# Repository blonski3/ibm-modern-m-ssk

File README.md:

# IBM Model M SSK Wireless
*Opracowanie i wykonanie układu sterującego klawiaturą mechaniczną*. Bezprzewodowa modernizacja IBM Model M SSK: nRF52840 + nPM1300, własna membrana FPC z diodą na klawisz, firmware ZMK.

## Struktura repozytorium

```
hardware/controller/   projekt KiCad 10: motherboard + daughterboard (jedna PCB, DB wyłamywany)
hardware/membrane/     projekt KiCad 10: membrana FPC, matryca 6 × 17
hardware/lib/          wspólna biblioteka: symbole, footprinty, modele 3D
docs/                  CHANGELOG.md, HARDWARE_DECISIONS.md, datasheets/, diagrams/
mechanics/             pomiary i eksporty z Onshape
reference/             projekty referencyjne (Nordic, FSSK v1.00)
tools/                 skrypty pomocnicze (np. check_3d_paths.py)
```

Decyzje projektowe i ich uzasadnienia: `docs/HARDWARE_DECISIONS.md`; historia zmian: `docs/CHANGELOG.md`.

## Resources

[Bolt Mod, A Comprehensive Tutorial: IBM Model M SSK 1991](https://imgur.com/gallery/bolt-mod-comprehensive-tutorial-ibm-model-m-ssk-1991-arUYken)

[FSSK v1.00 - Installation & Users Manual](https://deskthority.net/viewtopic.php?t=13551)

[Request for Permission to Integrate Zephyr PF1550 PMIC Drivers into ZMK #2958](https://github.com/zmkfirmware/zmk/issues/2958)

[nRF52840 Product Specification v1.5](https://docs.nordicsemi.com/viewer/book-attachment/de~7rocmcN70bRHnA4~zJA/H1GC97m6GZQEaMxKCN6OOg-de~7rocmcN70bRHnA4~zJA)

[nPM1300 Product Specification v1.3](https://docs.nordicsemi.com/viewer/book-attachment/ZO1FVHHS04YNNMSlbsZ0Kg/KbFbu1gXgIMOyTgBK7q46A-ZO1FVHHS04YNNMSlbsZ0Kg)

[Keyboard Layout Editor NG - IBM Model M](https://editor.keyboard-tools.xyz/#share=NobwRAhgrgLgFgewE5gFxgEYBsEDswA0YuEAtgKZpgCSAQgLIAEAyswNKP0IAm5WnhMAGcADhADGAS1wBzAPoBPNACYADADoAHABYAvgVCQ0q-WELgAHmgCMpwfaLmwV1BoCsdx17MFLx9R7eDj5+rgGePmYAugbgSqi2QUmRwanJDqHW4ekxhgDuNtkp6SXFZU4FCUVOLu4R9rnglVkA7IHlpWkdTSrqyu1gjWCVyn0DnRPFPVVtnqGjA0PN1b7ONkTL49Mtc8OFW2sJG-u7tSspQy7Wo21E8QC0AMy7y-12S4VvQUMPysdVi1ih2sekclxs2juaHuoOiUSAA)

[WR-PHD Pin Header drawing](https://www.we-online.com/components/products/datasheet/61300811021.pdf)

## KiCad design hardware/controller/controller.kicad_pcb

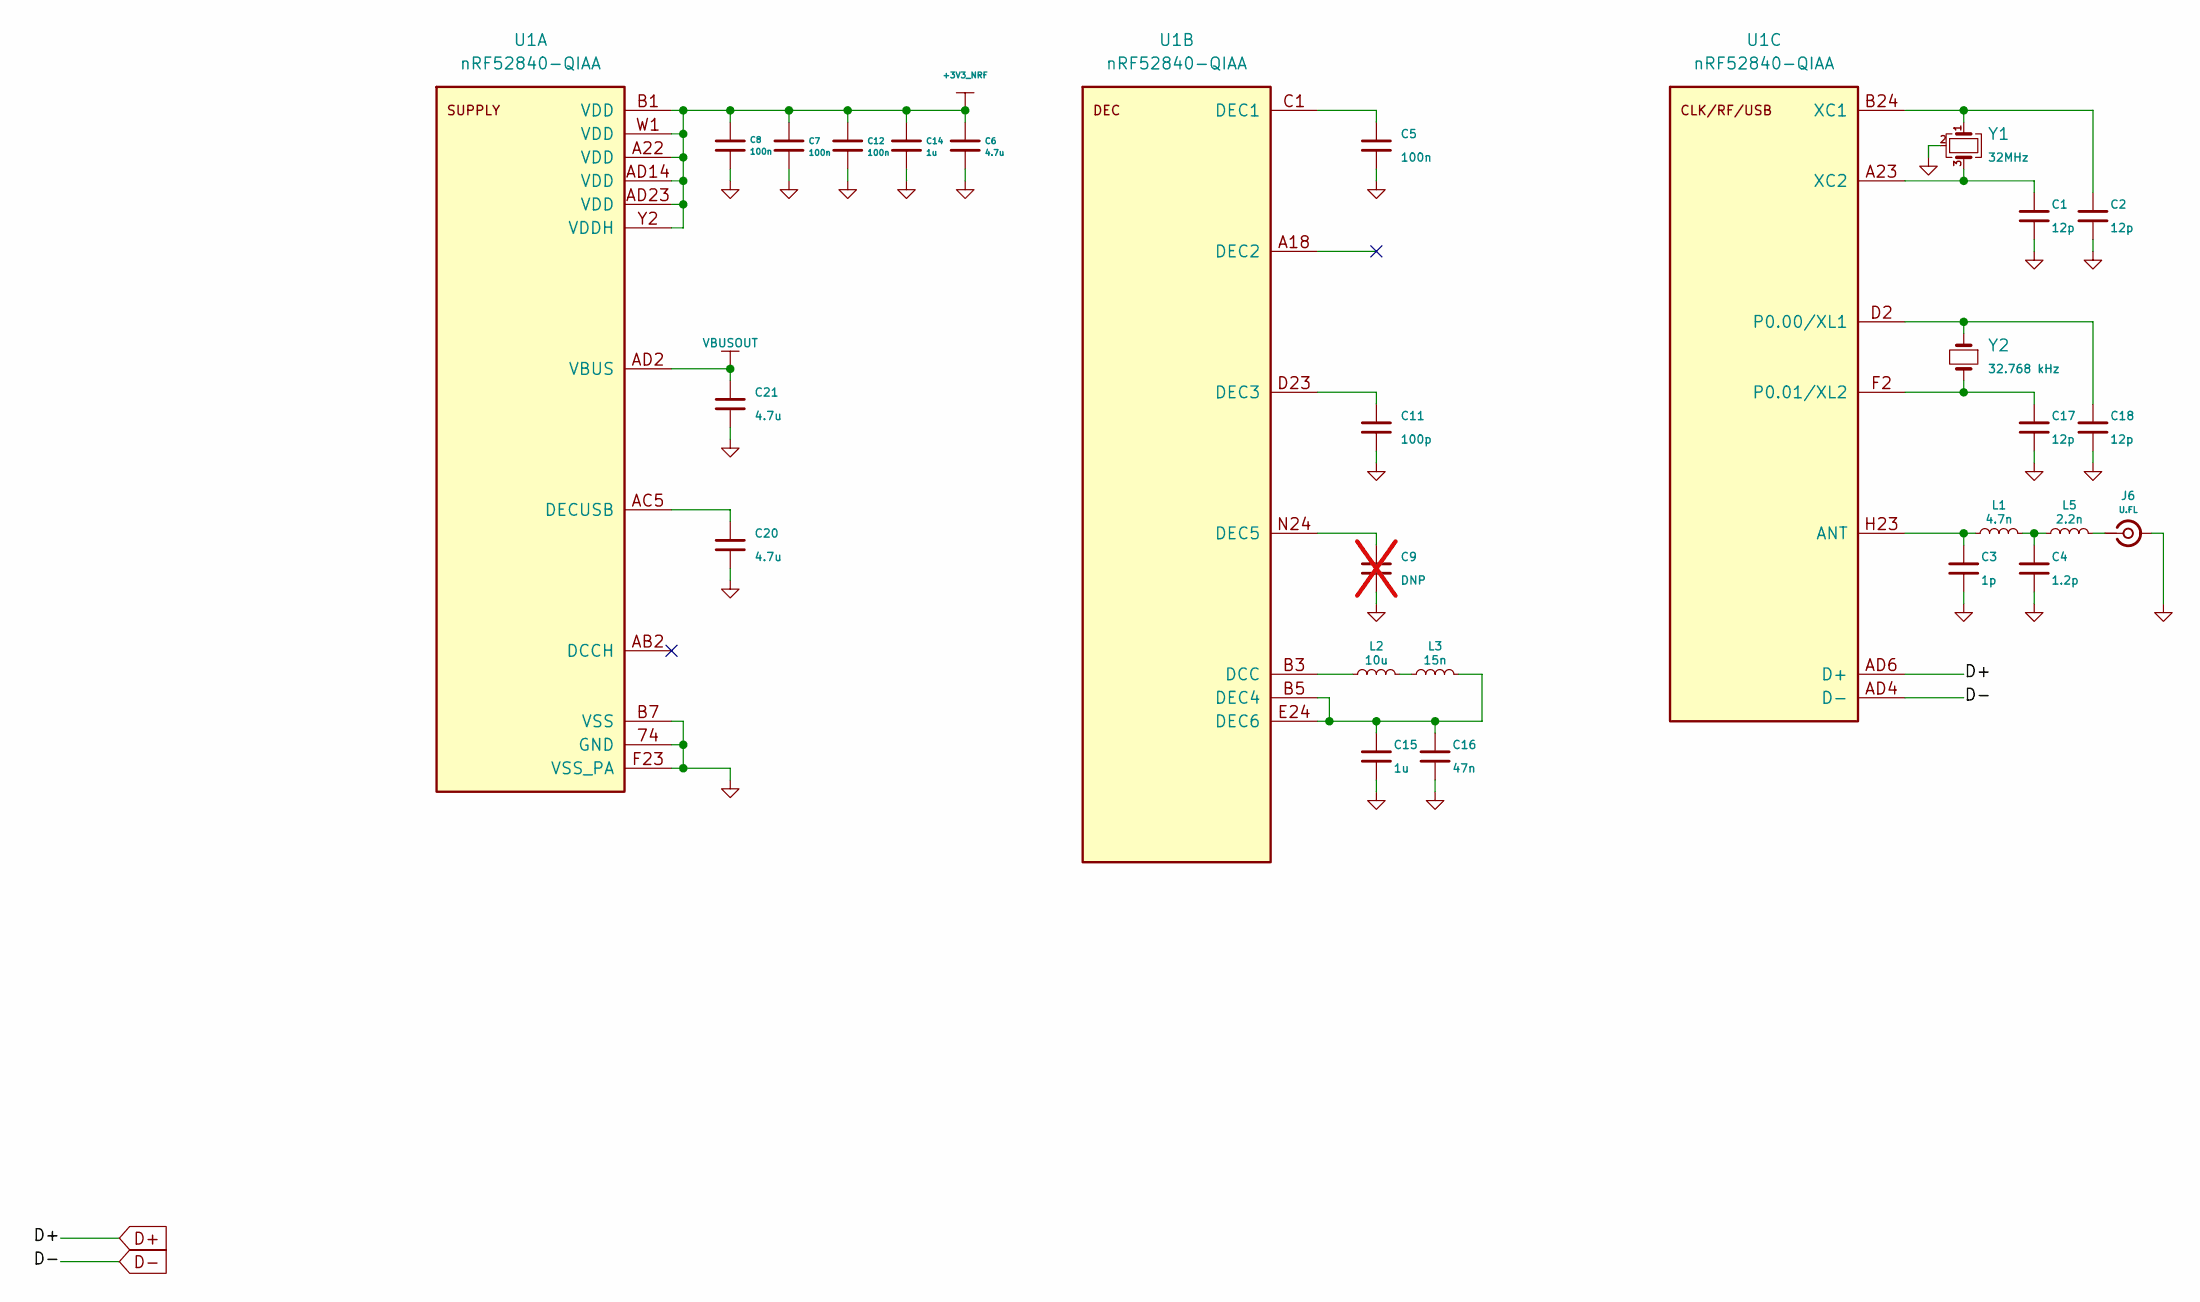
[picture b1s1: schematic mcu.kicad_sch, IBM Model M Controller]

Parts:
C1, C2, C17, C18: 12p; C_0402_1005Metric; PART NUMBER 0402CG120J500NT; LCSC Part C1547
C3: 1p; C_0402_1005Metric; PART NUMBER 0402CG1R0C500NT; LCSC Part C1550
C4: 1.2p; C_0402_1005Metric; PART NUMBER 0402CG1R2C500NT; LCSC Part C1551
C5, C7, C8, C12: 100n; C_0402_1005Metric; PART NUMBER CL05B104KO5NNNC; LCSC Part C1525
C6, C20, C21: 4.7u; C_0603_1608Metric; PART NUMBER CL10A475KO8NNNC; LCSC Part C19666
C9: DNP; C_0402_1005Metric; not fitted
C11: 100p; C_0402_1005Metric; PART NUMBER 0402CG101J500NT; LCSC Part C1546
C14, C15: 1u; C_0603_1608Metric; PART NUMBER CL10A105KB8NNNC; LCSC Part C15849
C16: 47n; C_0603_1608Metric; PART NUMBER CL10B473KB8NNNC; LCSC Part C1622
J6: U.FL; IPEX-SMD_4P-L2.6-W2.6-LS3.0_GT-RF1125A-01G; PART NUMBER U.FL-IPEX-1; LCSC Part C53433123
L1: 4.7n; L_0402_1005Metric; LCSC Part C304335
L2: 10u; L_0603_1608Metric; LCSC Part C86083
L3: 15n; L_0402_1005Metric; LCSC Part C381880
L5: 2.2n; L_0402_1005Metric; PART NUMBER CLH1005T-2N2S-S-NP; LCSC Part C142238
U1: nRF52840-QIAA; AQFN50P700X700X85_HS-74N; PART NUMBER NRF52840-QIAA-R; LCSC Part C190794
Y1: 32MHz; Crystal_SMD_2016-4Pin_2.0x1.6mm; PART NUMBER NX2016SA-32MHZ-EXS00A-CS06654; LCSC Part C5441424
Y2: 32.768 kHz; Crystal_SMD_3215-2Pin; LCSC Part C99010

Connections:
+3V3_NRF: C6.1, C7.1, C8.1, C12.1, C14.2, U1.A22 (VDD), U1.AD14 (VDD), U1.AD23 (VDD), U1.B1 (VDD), U1.W1 (VDD), U1.Y2 (VDDH); also elsewhere on the board
D+: U1.AD6 (D+); also elsewhere on the board
D-: U1.AD4 (D-); also elsewhere on the board
GND: C1.2, C2.1, C3.2, C4.2, C5.1, C6.2, C7.2, C8.2, C9.2, C11.1, C12.2, C14.1, C15.2, C16.2, C17.2, C18.1, C20.2, C21.2, J6.2 (Ext), U1.74 (GND), U1.B7 (VSS), U1.F23 (VSS_PA), Y1.2 (G), Y1.4 (G); also elsewhere on the board
unnamed: C4.1, L1.2, L5.1
unnamed: J6.1 (In), L5.2
unnamed: L2.1, L3.2
unnamed: C20.1, U1.AC5 (DECUSB)
unnamed: L2.2, U1.B3 (DCC)
unnamed: C5.2, U1.C1 (DEC1)
unnamed: C11.2, U1.D23 (DEC3)
unnamed: C15.1, C16.1, L3.1, U1.B5 (DEC4), U1.E24 (DEC6)
unnamed: C9.1, U1.N24 (DEC5)
unnamed: C3.1, L1.1, U1.H23 (ANT)
unnamed: C18.2, U1.D2 (P0.00/XL1), Y2.1
unnamed: C17.1, U1.F2 (P0.01/XL2), Y2.2
unnamed: C2.2, U1.B24 (XC1), Y1.1
unnamed: C1.1, U1.A23 (XC2), Y1.3
VBUSOUT: C21.1, U1.AD2 (VBUS); also elsewhere on the board

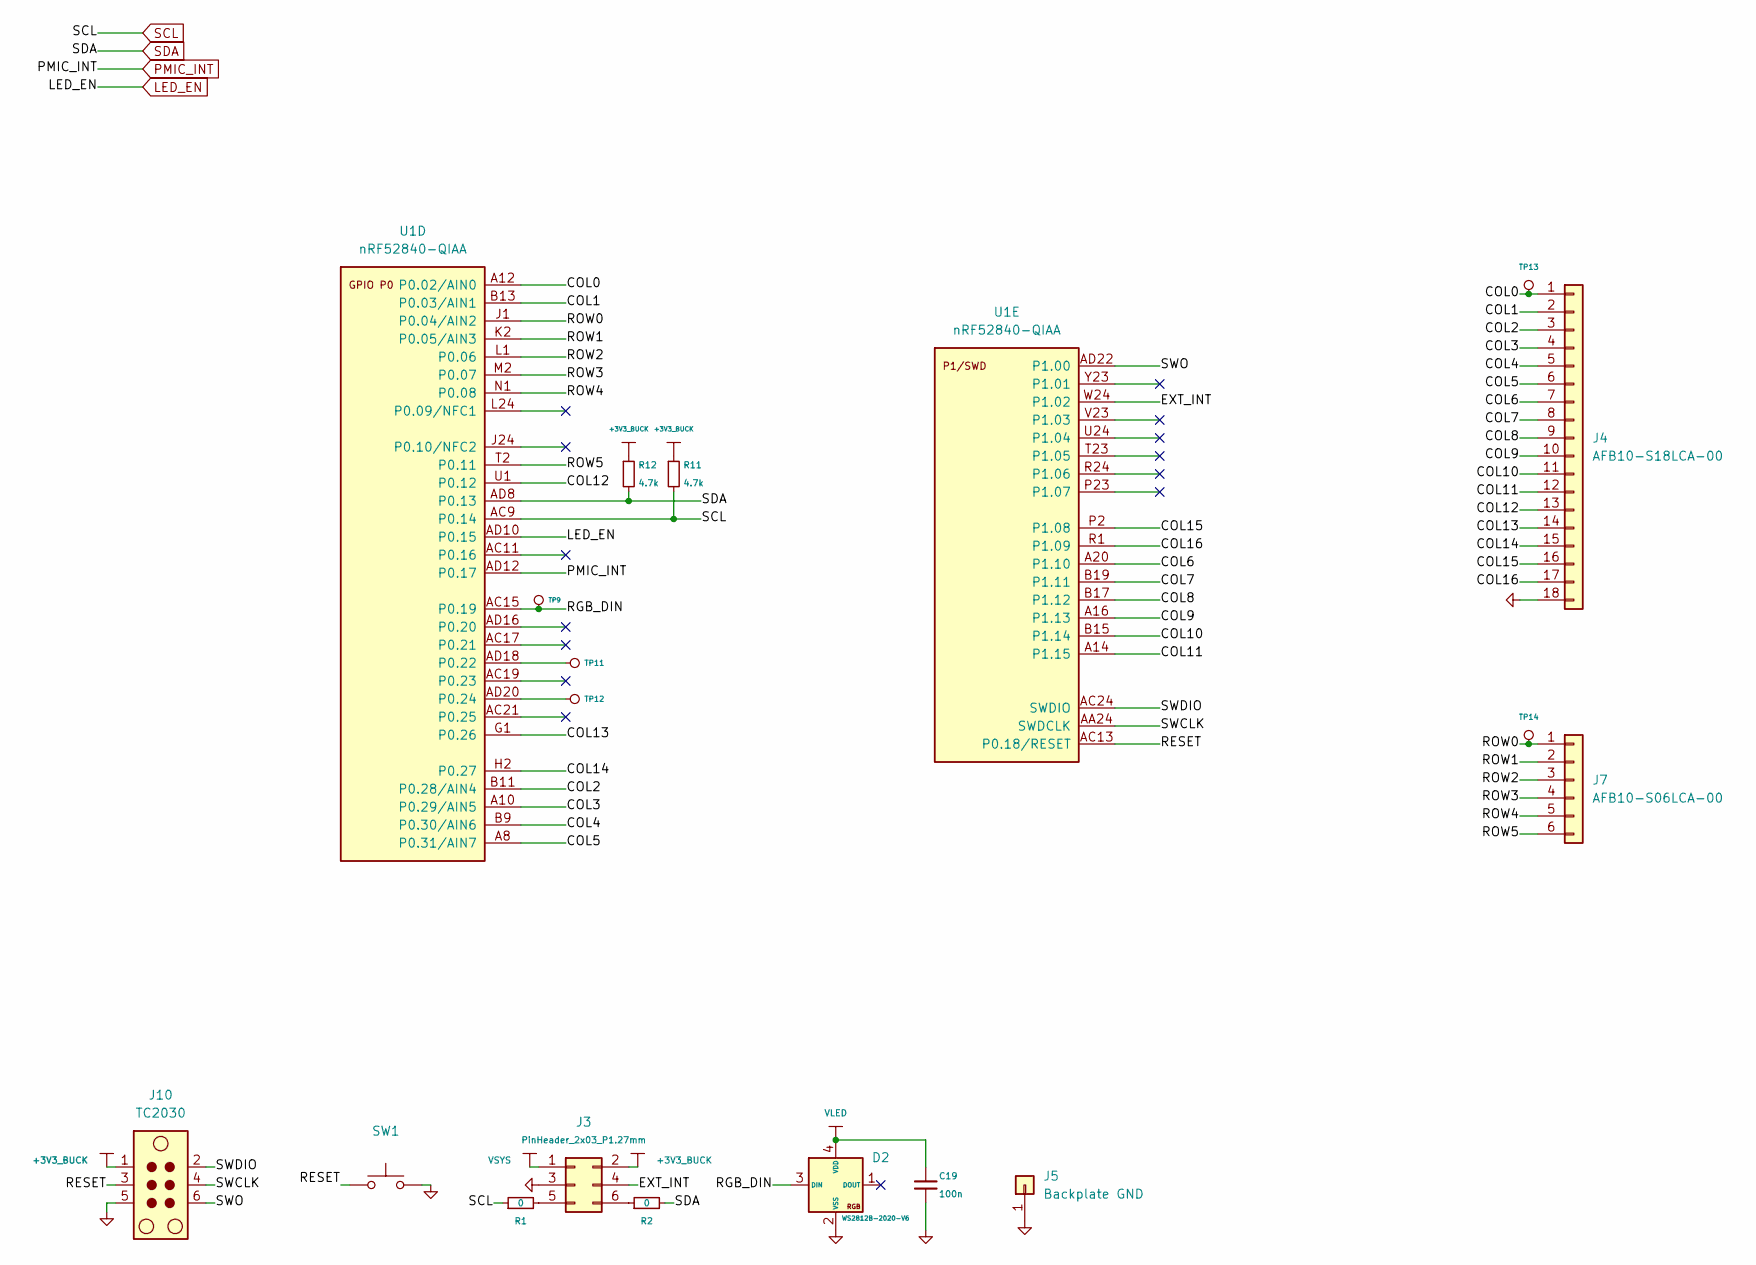
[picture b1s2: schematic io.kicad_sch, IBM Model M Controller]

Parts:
C19: 100n; C_0402_1005Metric; PART NUMBER CL05B104KO5NNNC; LCSC Part C1525
D2: WS2812B-2020-V6; LED-SMD_4P-L2.2-W2.0-P1.00_WS2815C-2020-4P; PART NUMBER WS2812B-2020-V6; LCSC Part C52917434
J3: PinHeader_2x03_P1.27mm; PinHeader_2x03_P1.27mm_Vertical_SMD
J4: AFB10-S18LCA-00; FPC-SMD_18P-P1.00_AFB10-S18LCA-00; PART NUMBER AFB10-S18LCA-00; LCSC Part C7499267
J5: Backplate GND; CONN-TH_726386-2; LCSC Part C305817
J7: AFB10-S06LCA-00; FPC-SMD_6P-P1.00_AFB10-S6LCA-00; PART NUMBER AFB10-S06LCA-00; LCSC Part C7499263
J10: TC2030; Tag-Connect_TC2030-IDC-NL_2x03_P1.27mm_Vertical
R1, R2: 0; R_0603_1608Metric; PART NUMBER 0603WAF0000T5E; LCSC Part C21189
R11, R12: 4.7k; R_0402_1005Metric; PART NUMBER 0402WGF4701TCE; LCSC Part C25900
SW1: SW_Push; SW-SMD_4P-L5.1-W5.1-P3.70-LS6.5-TL_H1.5; PART NUMBER TS-1187A-B-A-B; LCSC Part C318884
TP9, TP11, TP12, TP13, TP14: TestPoint; TestPoint_Pad
U1: nRF52840-QIAA; AQFN50P700X700X85_HS-74N; PART NUMBER NRF52840-QIAA-R; LCSC Part C190794

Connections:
+3V3_BUCK: J3.2, J10.1, R11.1, R12.1; also elsewhere on the board
/MCU IO/COL0: J4.1, TP13.1 (1_1), U1.A12 (P0.02/AIN0)
/MCU IO/COL1: J4.2, U1.B13 (P0.03/AIN1)
/MCU IO/COL2: J4.3, U1.B11 (P0.28/AIN4)
/MCU IO/COL3: J4.4, U1.A10 (P0.29/AIN5)
/MCU IO/COL4: J4.5, U1.B9 (P0.30/AIN6)
/MCU IO/COL5: J4.6, U1.A8 (P0.31/AIN7)
/MCU IO/COL6: J4.7, U1.A20 (P1.10)
/MCU IO/COL7: J4.8, U1.B19 (P1.11)
/MCU IO/COL8: J4.9, U1.B17 (P1.12)
/MCU IO/COL9: J4.10, U1.A16 (P1.13)
/MCU IO/COL10: J4.11, U1.B15 (P1.14)
/MCU IO/COL11: J4.12, U1.A14 (P1.15)
/MCU IO/COL12: J4.13, U1.U1 (P0.12)
/MCU IO/COL13: J4.14, U1.G1 (P0.26)
/MCU IO/COL14: J4.15, U1.H2 (P0.27)
/MCU IO/COL15: J4.16, U1.P2 (P1.08)
/MCU IO/COL16: J4.17, U1.R1 (P1.09)
/MCU IO/EXT_INT: J3.4, U1.W24 (P1.02)
/MCU IO/RESET: J10.3, SW1.1, U1.AC13 (P0.18/RESET)
/MCU IO/RGB_DIN: D2.3 (DIN), TP9.1 (1_1), U1.AC15 (P0.19)
/MCU IO/ROW0: J7.1, TP14.1 (1_1), U1.J1 (P0.04/AIN2)
/MCU IO/ROW1: J7.2, U1.K2 (P0.05/AIN3)
/MCU IO/ROW2: J7.3, U1.L1 (P0.06)
/MCU IO/ROW3: J7.4, U1.M2 (P0.07)
/MCU IO/ROW4: J7.5, U1.N1 (P0.08)
/MCU IO/ROW5: J7.6, U1.T2 (P0.11)
/MCU IO/SWCLK: J10.4, U1.AA24 (SWDCLK)
/MCU IO/SWDIO: J10.2, U1.AC24 (SWDIO)
/MCU IO/SWO: J10.6, U1.AD22 (P1.00)
GND: C19.2, D2.2 (VSS), J3.3, J4.18, J5.1 (Pin_1_1), J10.5, SW1.2; also elsewhere on the board
LED_EN: U1.AD10 (P0.15); also elsewhere on the board
unnamed: J3.5, R1.2
unnamed: J3.6, R2.1
unnamed: TP11.1 (1_1), U1.AD18 (P0.22)
unnamed: TP12.1 (1_1), U1.AD20 (P0.24)
PMIC_INT: U1.AD12 (P0.17); also elsewhere on the board
SCL: R1.1, R11.2, U1.AC9 (P0.14); also elsewhere on the board
SDA: R2.2, R12.2, U1.AD8 (P0.13); also elsewhere on the board
VLED: C19.1, D2.4 (VDD); also elsewhere on the board
VSYS: J3.1; also elsewhere on the board

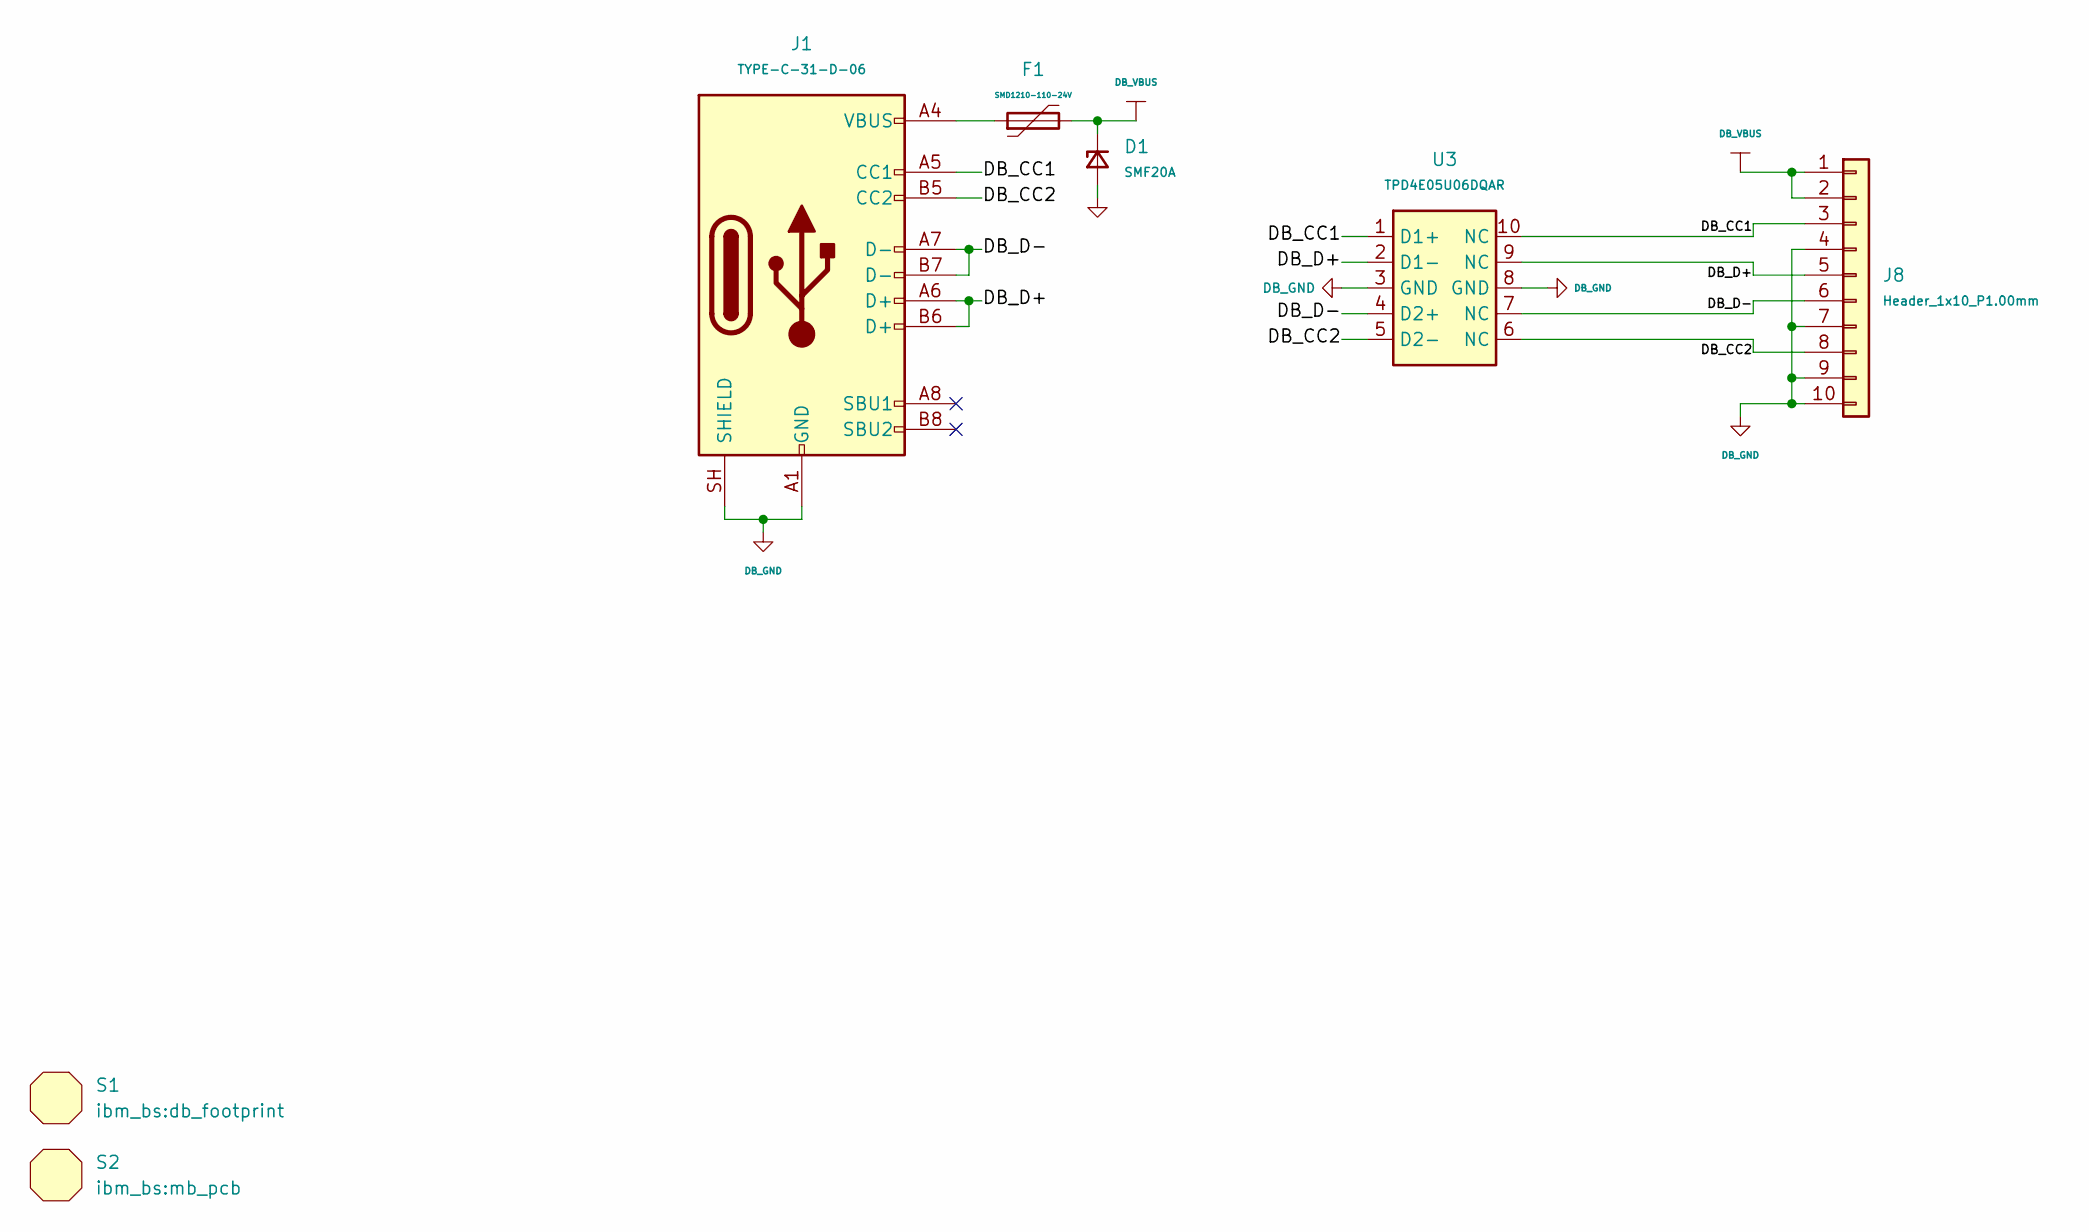
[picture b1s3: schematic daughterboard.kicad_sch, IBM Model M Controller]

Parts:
D1: SMF20A; D_SOD-123F; PART NUMBER SMF20A; LCSC Part C123788
F1: SMD1210-110-24V; Fuse_1210_3225Metric; PART NUMBER SMD1210-110-24V; LCSC Part C22436715
J1: TYPE-C-31-D-06; USB-C-SMD_TYPE-C-31-D-06; PART NUMBER TYPE-C-31-D-06; LCSC Part C2689964
J8: Header_1x10_P1.00mm; PinHeader_1x10_P1.00mm_Vertical_SMD_Pin1Left
S1: Mechanical_Shape; db_footprint
S2: Mechanical_Shape; mb_pcb
U3: TPD4E05U06DQAR; USON-10_2.5x1.0mm_P0.5mm; PART NUMBER TPD4E05U06DQAR; LCSC Part C138714

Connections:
/Daughterboard/DB_CC1: J1.A5 (CC1), J8.3, U3.1 (D1+), U3.10 (NC)
/Daughterboard/DB_CC2: J1.B5 (CC2), J8.8, U3.5 (D2-), U3.6 (NC)
/Daughterboard/DB_D+: J1.A6 (D+), J1.B6 (D+), J8.5, U3.2 (D1-), U3.9 (NC)
/Daughterboard/DB_D-: J1.A7 (D-), J1.B7 (D-), J8.6, U3.4 (D2+), U3.7 (NC)
DB_GND: D1.2 (A), J1.A1 (GND), J1.A12 (GND), J1.B1 (GND), J1.B12 (GND), J1.SH (SHIELD), J8.4, J8.7, J8.9, J8.10, U3.3 (GND), U3.8 (GND)
DB_VBUS: D1.1 (K), F1.2, J8.1, J8.2
unnamed: F1.1, J1.A4 (VBUS), J1.A9 (VBUS), J1.B4 (VBUS), J1.B9 (VBUS)

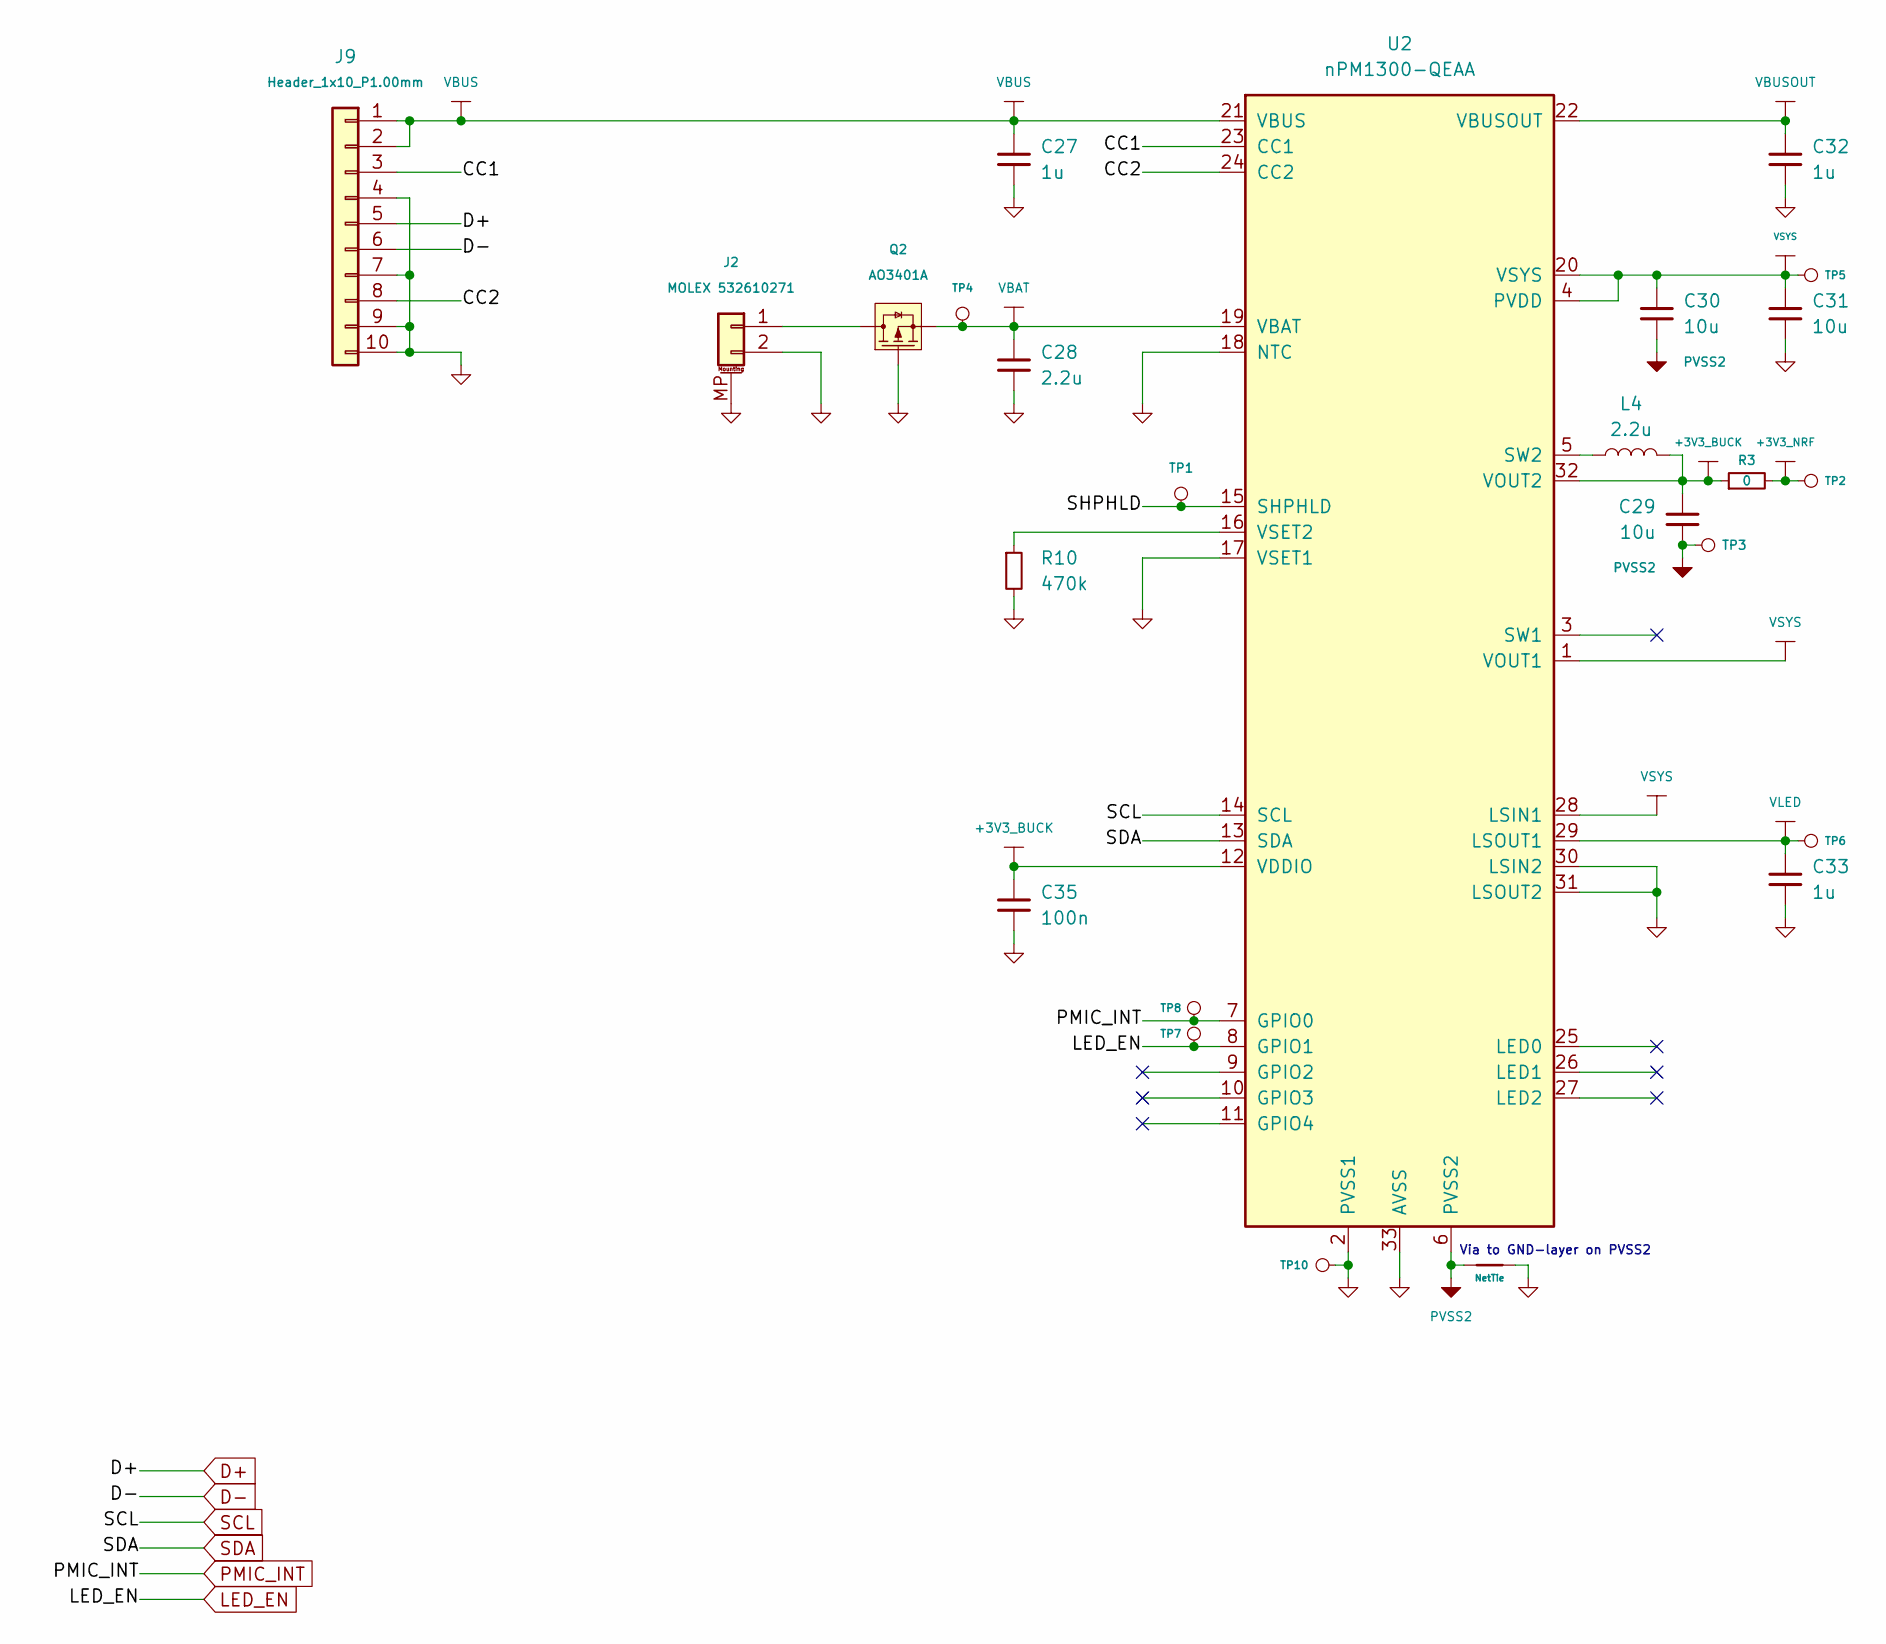
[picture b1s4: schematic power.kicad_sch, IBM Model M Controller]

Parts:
C27, C32, C33: 1u; C_0603_1608Metric; PART NUMBER CL10A105KB8NNNC; LCSC Part C15849
C28: 2.2u; C_0603_1608Metric; PART NUMBER CL10A225KO8NNNC; LCSC Part C23630
C29, C30, C31: 10u; C_0603_1608Metric; PART NUMBER CL10A106KP8NNNC; LCSC Part C19702
C35: 100n; C_0603_1608Metric; PART NUMBER CC0603KRX7R9BB104; LCSC Part C14663
J2: MOLEX 532610271; Molex_PicoBlade_53261-0271_1x02-1MP_P1.25mm_Horizontal; PART NUMBER 53261-0271; LCSC Part C177225
J9: Header_1x10_P1.00mm; PinHeader_1x10_P1.00mm_Vertical
L4: 2.2u; L_1008_2520Metric; LCSC Part C5349606
NT1: NetTie; NetTie-2_SMD_Via0.45mm
Q2: AO3401A; SOT-23; PART NUMBER AO3401A; LCSC Part C15127
R3: 0; R_0603_1608Metric; PART NUMBER 0603WAF0000T5E; LCSC Part C21189
R10: 470k; R_0603_1608Metric; PART NUMBER 0603WAF4703T5E; LCSC Part C23178
TP1, TP2, TP3, TP4, TP5, TP6, TP7, TP8, TP10: TestPoint; TestPoint_Pad
U2: nPM1300-QEAA; Nordic_QFN50P500X500X90-33N; LCSC Part C7466043

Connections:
+3V3_BUCK: C29.1, C35.1, L4.2, R3.1, U2.12 (VDDIO), U2.32 (VOUT2); also elsewhere on the board
+3V3_NRF: R3.2, TP2.1 (1_1); also elsewhere on the board
/Power/CC1: J9.3, U2.23 (CC1)
/Power/CC2: J9.8, U2.24 (CC2)
/Power/SHPHLD: TP1.1 (1_1), U2.15 (SHPHLD)
D+: J9.5; also elsewhere on the board
D-: J9.6; also elsewhere on the board
GND: C27.2, C28.2, C31.2, C32.2, C33.2, C35.2, J2.2, J2.MP (MountPin), J9.4, J9.7, J9.9, J9.10, NT1.1, Q2.1 (G), R10.2, TP10.1 (1_1), U2.2 (PVSS1), U2.17 (VSET1), U2.18 (NTC), U2.30 (LSIN2), U2.31 (LSOUT2), U2.33 (AVSS); also elsewhere on the board
LED_EN: TP7.1 (1_1), U2.8 (GPIO1); also elsewhere on the board
unnamed: J2.1, Q2.3 (D)
unnamed: L4.1, U2.5 (SW2)
unnamed: R10.1, U2.16 (VSET2)
PMIC_INT: TP8.1 (1_1), U2.7 (GPIO0); also elsewhere on the board
PVSS2: C29.2, C30.2, NT1.2, TP3.1 (1_1), U2.6 (PVSS2)
SCL: U2.14 (SCL); also elsewhere on the board
SDA: U2.13 (SDA); also elsewhere on the board
VBAT: C28.1, Q2.2 (S), TP4.1 (1_1), U2.19 (VBAT)
VBUS: C27.1, J9.1, J9.2, U2.21 (VBUS)
VBUSOUT: C32.1, U2.22 (VBUSOUT); also elsewhere on the board
VLED: C33.1, TP6.1 (1_1), U2.29 (LSOUT1); also elsewhere on the board
VSYS: C30.1, C31.1, TP5.1 (1_1), U2.1 (VOUT1), U2.4 (PVDD), U2.20 (VSYS), U2.28 (LSIN1); also elsewhere on the board

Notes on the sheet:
Via to GND-layer on PVSS2

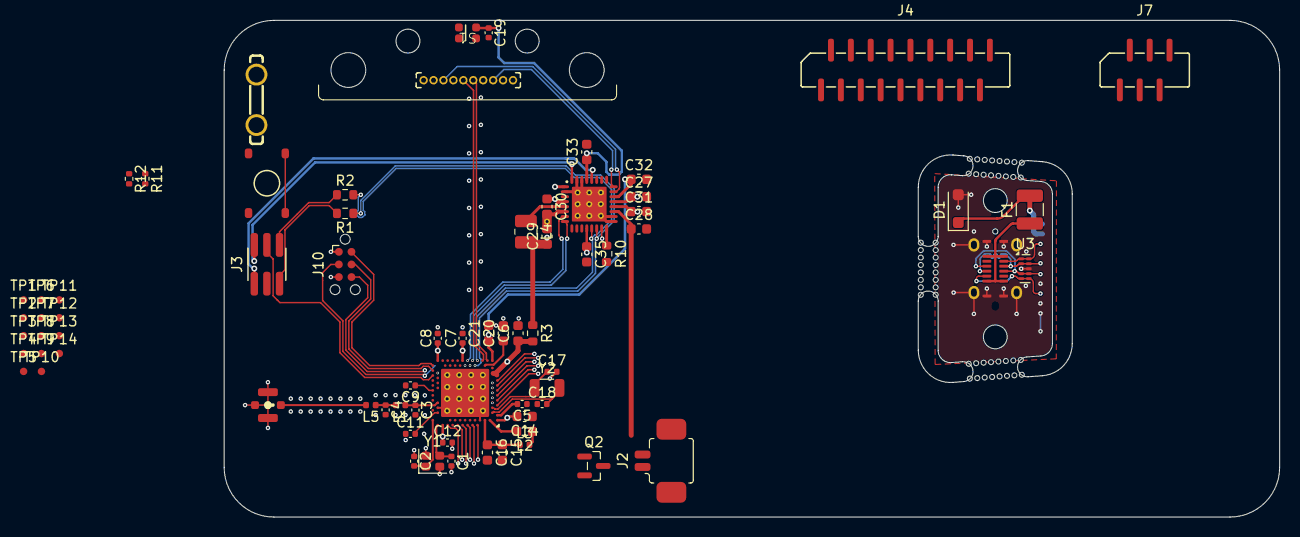
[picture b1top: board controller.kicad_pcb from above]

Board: 4 copper layers, 106.2 x 50.0 mm, 75 parts (1 on the bottom side), 75 nets.

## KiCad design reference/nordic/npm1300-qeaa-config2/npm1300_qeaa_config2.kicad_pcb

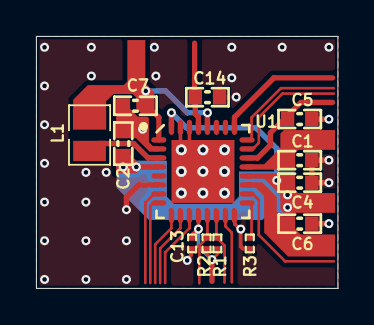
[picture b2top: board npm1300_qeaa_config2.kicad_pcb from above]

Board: 4 copper layers, 16.8 x 14.0 mm, 14 parts (0 on the bottom side), 13 nets.

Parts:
C1, C5, C14: 1.0µF; CAPC1608X06L
C2, C4, C7: 10µF; CAPC1608X06L
C6: 2.2µF; CAPC1608X06L
C13: 100nF; CAPC0603X03L_C
L1: 2.2µH; INDC2016X10N
NT1: Net tie; 2 PIN STARPOINT
R1, R2: 10k; RESC0603X03L_C
R3: 47k; RESC0603X03L_C
U1: nPM1300-QEAA; Nordic_QFN50P500X500X90-33N

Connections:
GND: C1.1, C4.1, C5.1, C6.1, C13.2, C14.1, NT1.1, R3.2, U1.6, U1.16, U1.30, U1.31, U1.33
LSOUT1: C14.2, U1.29
PVSS1: C2.1, C7.1, NT1.2, U1.2
SCL: R1.1, U1.14
SDA: R2.1, U1.13
SW1: L1.2, U1.3
VBAT: C6.2, U1.19
VBUSIN: C1.2, U1.21
VBUSOUT: C5.2, U1.22
VDDIO: C13.1, R1.2, R2.2, U1.12
VOUT1: C7.2, L1.1, U1.1, U1.28
VSET1: R3.1, U1.17
VSYS: C2.2, C4.2, U1.4, U1.20, U1.32

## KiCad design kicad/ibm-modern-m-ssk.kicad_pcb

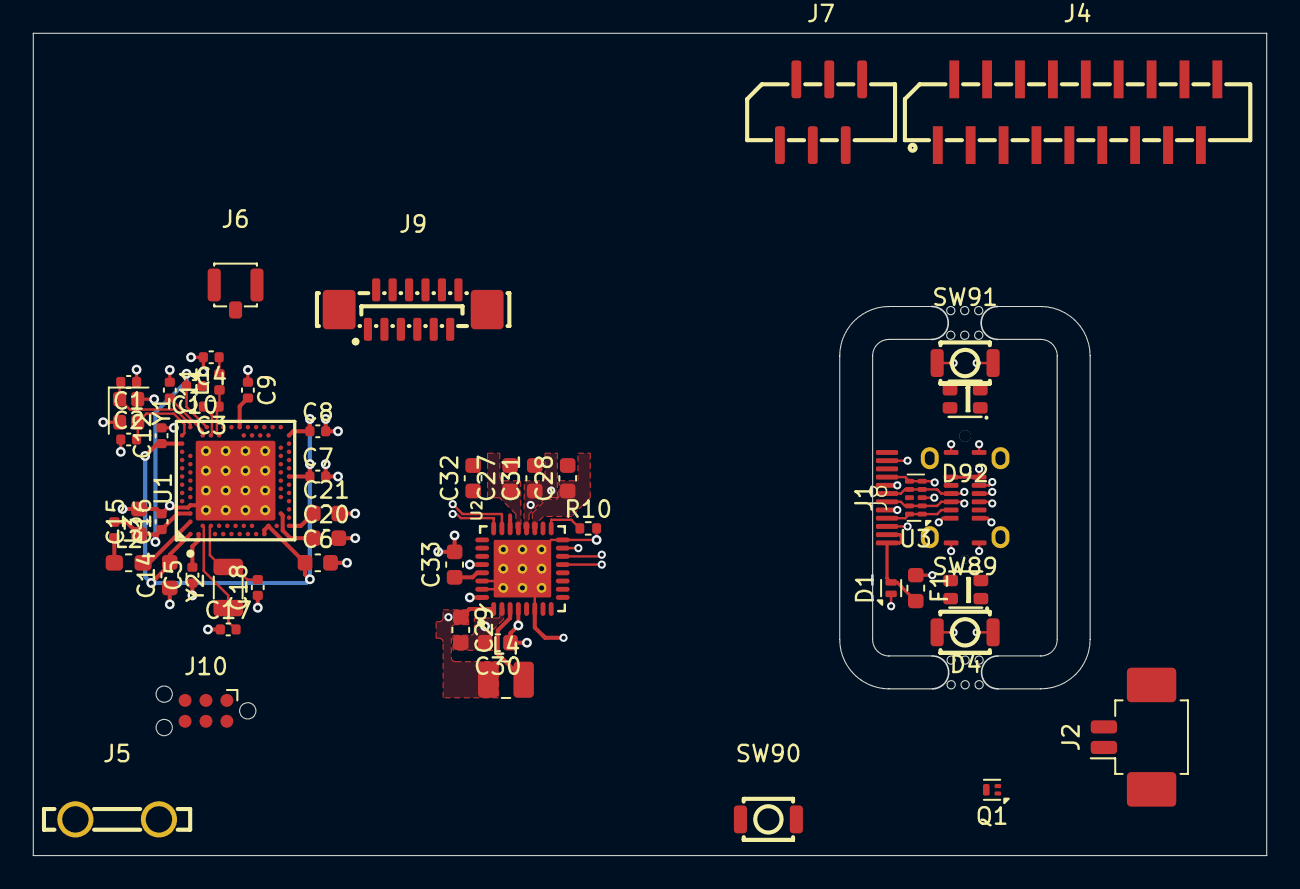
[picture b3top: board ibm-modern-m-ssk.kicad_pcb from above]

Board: 4 copper layers, 75.0 x 50.0 mm, 53 parts (0 on the bottom side), 35 nets.

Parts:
C1, C2, C17, C18: 12p; C_0402_1005Metric
C3: 0.8p; C_0402_1005Metric
C4: 0.5p; C_0402_1005Metric
C5, C7, C8, C12: 100n; C_0402_1005Metric
C6, C20, C21: 4.7u; C_0603_1608Metric
C9: 820p; C_0402_1005Metric
C10: NC; C_0402_1005Metric
C11: 100p; C_0402_1005Metric
C14, C15, C27, C32, C33: 1u; C_0603_1608Metric
C16: 47n; C_0402_1005Metric
C28: 2.2u; C_0603_1608Metric
C29, C30, C31: 10u; C_0603_1608Metric
D1: PESDNC2FD5VB; Diodes_DFN1006-2
D4, D92: rgb; WS2812C-2020-V1
F1: BSMD0603L-150; Fuse_0603_1608Metric
J1: TYPE-C-31-D-06; USB-C-SMD_TYPE-C-31-D-06
J2: Molex PicoBlade; Molex_PicoBlade_53261-0271_1x02-1MP_P1.25mm_Horizontal
J4: AFB10-S18LCA-00; FPC-SMD_18P-P1.00_AFB10-S18LCA-00
J5: 726386-2; CONN-TH_726386-2
J6: Conn_Coaxial_Small; IPEX-SMD_3P-L2.6-W2.6-LS3.0_ZCF-CF0001-0002IPEX
J7: AFB10-S06LCA-00; FPC-SMD_6P-P1.00_AFB10-S6LCA-00
J8: FPC_12P_0.5mm
J9: AFC11-S12ICA-00; CONN-SMD-12P_AFC11-S12ICA-00
J10: TC2030; Tag-Connect_TC2030-IDC-NL_2x03_P1.27mm_Vertical
L1: 4.7n; L_0402_1005Metric
L2: 10u; L_0603_1608Metric_Pad1.05x0.95mm_HandSolder
L3: 15n; L_0402_1005Metric
L4: 2.2u; L_1008_2520Metric
Q1: PMZB350UPE,315; DFN1006-3
R10: 470k; R_0402_1005Metric
SW89, SW90, SW91: SW_Push; KEY-SMD_B3U-1000PM
U1: NRF52840; AQFN50P700X700X85_HS-74N
U2: nPM1300-QEAA; Nordic_QFN50P500X500X90-33N
U3: TPD4E05U06DQAR; USON-10_2.5x1.0mm_P0.5mm
Y1: 32MHz; Crystal_SMD_2016-4Pin_2.0x1.6mm
Y2: 32.768 kHz; Crystal_SMD_3215-2Pin

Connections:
/daughterboard/BT_PAIR: J8.3, J9.3, SW89.1
/daughterboard/CC1: J1.A5 (CC1), J8.4, J9.4, U2.23 (CC1), U3.1 (D1+), U3.10 (NC)
/daughterboard/CC2: J1.B5 (CC2), J8.9, J9.9, U2.24 (CC2), U3.5 (D2-), U3.6 (NC)
/daughterboard/LED_DATA: D4.3 (DIN), J8.10, J9.10
/daughterboard/SHPHLD: J8.11, J9.11, SW91.1, U2.15 (SHPHLD)
/motherboard/ANTENNA: C4.1, J6.1 (In), L1.2
/motherboard/DEC4: C10.2, C15.1, C16.1, L3.1, U1.B5 (DEC4), U1.E24 (DEC6)
/motherboard/SWCLK: J10.4, U1.AA24 (SWDCLK)
/motherboard/SWDIO: J10.2, U1.AC24 (SWDIO)
D+: J1.A6 (D+), J1.B6 (D+), J8.6, J9.6, U1.AD6 (D+), U3.2 (D1-), U3.9 (NC)
D-: J1.A7 (D-), J1.B7 (D-), J8.7, J9.7, U1.AD4 (D-), U3.4 (D2+), U3.7 (NC)
GND: C1.1, C2.1, C3.2, C4.2, C5.1, C6.2, C7.2, C8.2, C9.2, C10.1, C11.1, C12.2, C14.1, C15.2, C16.2, C17.1, C18.1, C20.2, C21.2, C27.2, C28.2, C31.2, C32.2, C33.2, D1.1 (A1), D4.2 (VSS), D92.2 (VSS), J1.A1 (GND), J1.A12 (GND), J1.B1 (GND), J1.B12 (GND), J2.2, J5.1, J6.2 (Ext), J8.5, J8.8, J9.5, J9.8, J10.3, J10.5, Q1.1 (G), R10.2, SW89.2, SW90.2, SW91.2, U1.74 (GND), U1.B7 (VSS), U1.F23 (VSS_PA), U2.6 (PVSS2), U2.16 (VSET2), U2.30 (LSIN2/VINLDO2), U2.31 (LSOUT2/VOUTLDO2), U2.33 (AVSS), U3.3 (GND), U3.8 (GND), Y1.2, Y1.4
unnamed: D4.1 (DOUT), D92.3 (DIN)
unnamed: F1.1, J1.A4 (VBUS), J1.A9 (VBUS), J1.B4 (VBUS), J1.B9 (VBUS)
unnamed: L2.1, L3.2
unnamed: J2.1, Q1.2 (S)
unnamed: C3.1, L1.1, U1.H23 (ANT)
unnamed: L2.2, U1.B3 (DCC)
unnamed: C5.2, U1.C1 (DEC1)
unnamed: C11.2, U1.D23 (DEC3)
unnamed: C9.1, U1.N24 (DEC5)
unnamed: C20.1, U1.AC5 (DECUSB)
unnamed: C17.2, U1.D2 (P0.00/XL1), Y2.2
unnamed: C18.2, U1.F2 (P0.01/XL2), Y2.1
unnamed: C1.2, U1.B24 (XC1), Y1.3
unnamed: C2.2, U1.A23 (XC2), Y1.1
unnamed: C33.1, U2.29 (LSOUT1/VOUTLDO1)
unnamed: L4.2, U2.3 (SW1)
unnamed: R10.1, U2.17 (VSET1)
PVSS1: C29.2, C30.2, U2.2 (PVSS1)
VBAT: C28.1, Q1.3 (D), U2.19 (VBAT)
VBUS: C27.1, D1.2 (A2), F1.2, J8.1, J8.2, J9.1, J9.2, U2.21 (VBUS)
VBUSOUT: C21.1, C32.1, U1.AD2 (VBUS), U2.22 (VBUSOUT)
VDD_NRF: C6.1, C7.1, C8.1, C12.1, C14.2, C29.1, J10.1, L4.1, U1.A22 (VDD), U1.AD14 (VDD), U1.AD23 (VDD), U1.B1 (VDD), U1.W1 (VDD), U1.Y2 (VDDH), U2.1 (VOUT1), U2.28 (LSIN1/VINLDO1)
VSYS: C30.1, C31.1, D4.4 (VDD), D92.4 (VDD), J8.12, J9.12, U2.4 (PVDD), U2.20 (VSYS), U2.32 (VOUT2)

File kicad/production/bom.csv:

Designator,Footprint,Quantity,Value,LCSC Part #
"C1, C17, C18, C2",0402,4,12p,C526985
"C10, C13, C22",0402,3,NC,~
C11,0402,1,100p,C106200
"C12, C5, C7, C8",0402,4,100n,C60474
"C14, C15, C27, C32, C33",0603,5,1u,C559769
C16,0402,1,47n,C327054
"C20, C21, C6",0603,3,4.7u,C277476
C28,0603,1,2.2u,C309478
"C29, C30, C31",0603,3,10u,C596327
C3,0402,1,0.8p,C326068
C4,0402,1,0.5p,C327230
C9,0402,1,820p,C726612
D2,LED-SMD_4P-L1.6-W1.5-TR-1,1,LED_RGB,C3029071
E1,SON-6_L1.4-W1.0-P0.50-TL_USBULC6-2M6,1,TPD2E001DRYR-TP,C2923399
J1,FPC-SMD_24P-P0.50_TF38-24S-0.5SV-830,1,TF38-24S-0.5SV(830),C3020653
J2,CONN-SMD_2P-P1.00_SM02B-SRSS-TB-LF-SN,1,S2B-PH-SM4-TB(LF)(SN),C160402
J5,CONN-TH_726386-2,1,726386-2,C305817
L1,0402,1,4.7n,C304335
L2,0603,1,10u,C86083
L3,0402,1,15n,C381880
L4,1008,1,2.2u,C5349606 
Q1,SOT-23-3_L2.9-W1.3-P1.90-LS2.4-BR,1,DMP2123LQ,C3647032
R1,0402,1,10k,C25744
R10,0402,1,470k,C25792
"R8, R9",0402,2,5.1k,C25905
SW90,SW-SMD_L3.9-W3.0-P4.45,1,SW_Push,C720477
U1,AQFN50P700X700X85_HS-74N,1,NRF52840,C190794
U2,Nordic_QFN50P500X500X90-33N,1,nPM1300-QEAA,C7466043
USBC1,USB-C_SMD-TYPE-C-31-M-12_1,1,TYPE-C-31-M-12,C165948
Y1,Crystal_SMD_2016-4Pin_2.0x1.6mm,1,32MHz,C255896
Y2,Crystal_SMD_3215-2Pin_3.2x1.5mm,1,32.768 kHz,C99010

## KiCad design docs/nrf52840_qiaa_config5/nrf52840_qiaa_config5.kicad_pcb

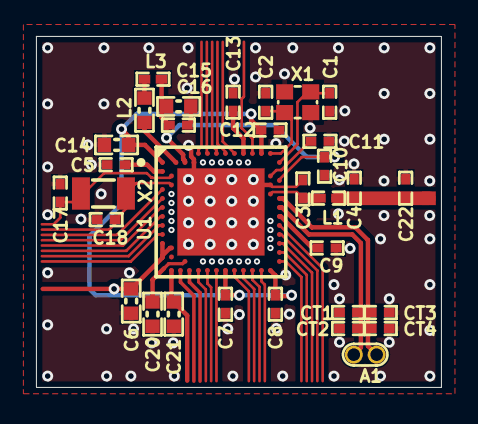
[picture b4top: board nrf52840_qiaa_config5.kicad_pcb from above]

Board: 4 copper layers, 22.5 x 19.5 mm, 32 parts (0 on the bottom side), 19 nets.

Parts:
A1: NFC Antenna; TP_2x1mm_TH
C1, C2, C17, C18: 12pF; CAPC1005X04L
C3: 0.8pF; CAPC1005X04L
C4: 0.5pF; CAPC1005X04L
C5, C7, C8, C12: 100nF; CAPC1005X04L
C6, C20, C21: 4.7µF; CAPC1608X06L
C9: 820pF; CAPC1005X04L
C10, C13, C22: N.C.; CAPC1005X04L
C11: 100pF; CAPC1005X04L
C14, C15: 1.0µF; CAPC1608X06L
C16: 47nF; CAPC1005X04L
CT1, CT2, CT3, CT4: Antenna dependent; CAPC1005X04L
L1: 4.7nH; INDC1005X04L
L2: 10µH; INDC1608X06L
L3: 15nH; INDC1005X04L
U1: nRF52840-QIAA; AQFN50P700X700X85_HS-74N
X1: 32MHz; BT-XTAL_2016
X2: 32.768kHz; XTAL_3215

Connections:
DEC1: C5.1, U1.C1
DEC3: C11.1, U1.D23
DEC4_6: C10.2, C15.2, C16.1, L3.1, U1.B5, U1.E24
GND: C1.2, C2.2, C3.1, C4.1, C5.2, C6.2, C7.2, C8.2, C9.2, C10.1, C11.2, C12.2, C13.2, C14.2, C15.1, C16.2, C17.2, C18.2, C20.2, C21.2, C22.2, CT1.2, CT2.2, CT3.1, CT4.1, U1.74, U1.B7, U1.F23, X1.2, X1.4
NFC1: A1.2, CT1.1, CT2.1, U1.L24
NFC2: A1.1, CT3.2, CT4.2, U1.J24
NetC3_2: C3.2, L1.1, U1.H23
NetC9_1: C9.1, U1.N24
NetC13_1: C13.1, U1.A18
NetC20_1: C20.1, U1.AC5
NetL2_1: L2.1, L3.2
NetL2_2: L2.2, U1.B3
P0.00/XL1: C17.1, U1.D2, X2.1
P0.01/XL2: C18.1, U1.F2, X2.2
RF: C4.2, C22.1, L1.2
VBUS: C21.1, U1.AD2
VDD_NRF: C6.1, C7.1, C8.1, C12.1, C14.1, U1.A22, U1.AD14, U1.AD23, U1.B1, U1.W1, U1.Y2
XC1: C1.1, U1.B24, X1.1
XC2: C2.1, U1.A23, X1.3
